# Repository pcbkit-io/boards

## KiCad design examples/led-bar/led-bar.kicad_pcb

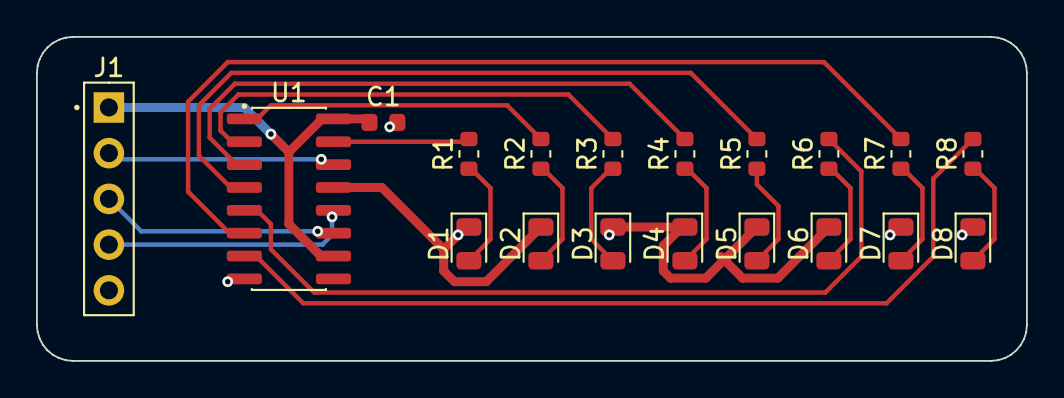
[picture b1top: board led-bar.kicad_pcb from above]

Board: 2 copper layers, 55.0 x 18.0 mm, 19 parts (0 on the bottom side), 21 nets.

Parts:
C1: 100nF; C_0603_1608Metric
D1, D2, D3, D4, D5, D6, D7, D8: green; LED_0805_2012Metric
J1: PinHeader_1x05_P2.54mm_Vertical
R1, R2, R3, R4, R5, R6, R7, R8: 470ohm; R_0603_1608Metric
U1: SN74HC595DR; SOIC-16_3.9x9.9mm_P1.27mm

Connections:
+5V: C1.1 (a), J1.1, U1.10 (SRCLR), U1.16 (VCC)
GND: C1.2 (b), D1.1 (K), D2.1 (K), D3.1 (K), D4.1 (K), D5.1 (K), D6.1 (K), D7.1 (K), D8.1 (K), J1.5, U1.8 (GND), U1.13 (OE)
Q0: R1.2 (b), U1.15 (QA)
Q1: R2.2 (b), U1.1 (QB)
Q2: R3.2 (b), U1.2 (QC)
Q3: R4.2 (b), U1.3 (QD)
Q4: R5.2 (b), U1.4 (QE)
Q5: R6.2 (b), U1.5 (QF)
Q6: R7.2 (b), U1.6 (QG)
Q7: R8.2 (b), U1.7 (QH)
RCLK: J1.4, U1.12 (RCLK)
SER: J1.2, U1.14 (SER)
SRCLK: J1.3, U1.11 (SRCLK)
leds[1]/anode: D1.2 (A), R1.1 (a)
leds[2]/anode: D2.2 (A), R2.1 (a)
leds[3]/anode: D3.2 (A), R3.1 (a)
leds[4]/anode: D4.2 (A), R4.1 (a)
leds[5]/anode: D5.2 (A), R5.1 (a)
leds[6]/anode: D6.2 (A), R6.1 (a)
leds[7]/anode: D7.2 (A), R7.1 (a)
leds[8]/anode: D8.2 (A), R8.1 (a)

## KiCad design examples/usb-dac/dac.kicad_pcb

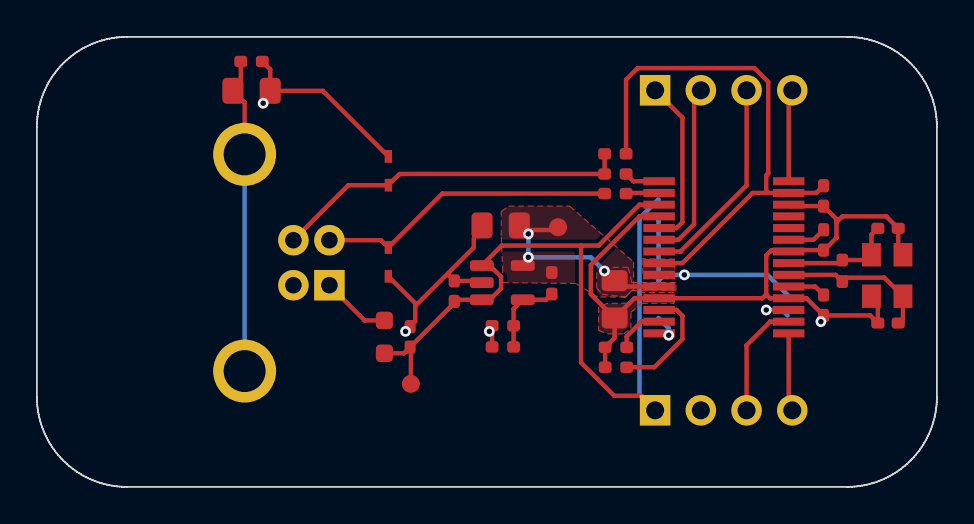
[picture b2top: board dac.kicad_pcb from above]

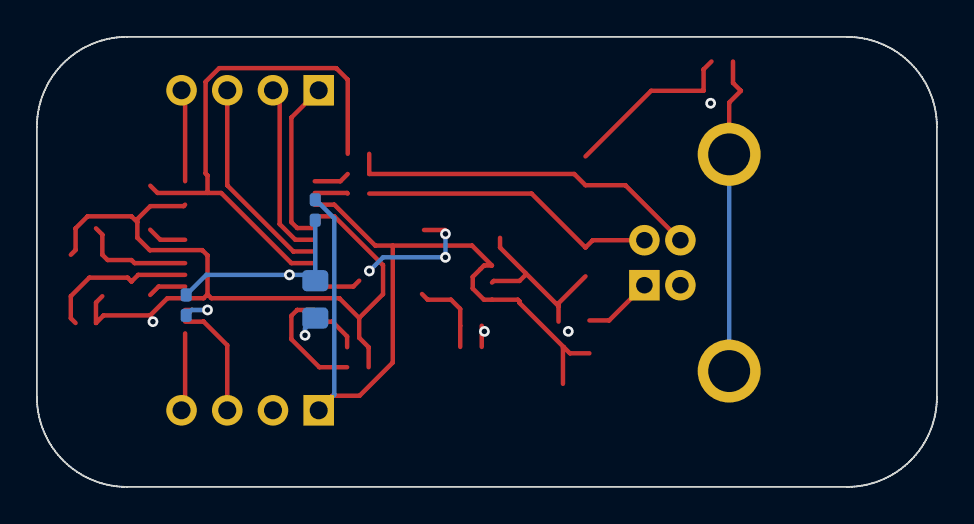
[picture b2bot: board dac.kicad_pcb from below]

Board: 4 copper layers, 50.0 x 25.0 mm, 34 parts (3 on the bottom side), 25 nets.

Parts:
C1, C6, C12: 10u; C_0805_2012Metric_Pad1.18x1.45mm_HandSolder
C2, C3, C4, C5, C7, C11, C13: 1u; C_0402_1005Metric_Pad0.74x0.62mm_HandSolder
C8, C9: 20p; C_0402_1005Metric_Pad0.74x0.62mm_HandSolder
C10: 2n2; C_0805_2012Metric_Pad1.18x1.45mm_HandSolder
D1, D2: ESD321; SOT5x3_DYA_TEX-M
J1: USB_B; USB_B_OST_USB-B1HSxx_Horizontal
J2, J3: Conn_01x04_Pin; PinHeader_1x04_P2.54mm_Vertical
R1, R2: 22R; R_0402_1005Metric_Pad0.72x0.64mm_HandSolder
R3, R4, R6: 1k5; R_0402_1005Metric_Pad0.72x0.64mm_HandSolder
R5: 1M; R_0402_1005Metric_Pad0.72x0.64mm_HandSolder
R7: DNP; R_0402_1005Metric_Pad0.72x0.64mm_HandSolder
R8: 2.2; R_0603_1608Metric_Pad0.98x0.95mm_HandSolder
R9, R10, R11: 10k; R_0402_1005Metric_Pad0.72x0.64mm_HandSolder
TP1, TP2: TestPoint; TestPoint_Pad_D1.0mm
U1: PCM2906C; SSOP-28_5.3x10.2mm_P0.65mm
U2: SPX3819M5-L; SOT-23-5
Y1: 12MHz; XTAL_ABM8-12.000MHZ-12-B1U-T

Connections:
3V7: C6.1, C12.1, R10.1, TP1.1, U1.10, U2.5
/ADJ: R9.1, R10.2, R11.1, U2.4
/CONN_D+: D2.2, J1.3, R1.1, R6.2
/CONN_D-: D1.2, J1.2, R2.1
/HID0: J3.1, U1.5
/HID1: J3.2, U1.6
/HID2: J3.3, U1.7
/USB_D+: R1.2, U1.1
/USB_D-: R2.2, U1.2
/VCCP1I: C2.1, U1.17
/VCCP2I: C3.1, U1.19
/VCCXI: C4.1, U1.23
/VCOM: C1.1, U1.14
/VINL: R4.1, U1.12
/VINR: R3.1, U1.13
/VOUTL: J2.3, U1.16
/VOUTR: J2.4, U1.15
/XTI: C9.1, R5.2, U1.21, Y1.3
/XTO: C8.1, R5.1, U1.20, Y1.1
/~SSPND: J3.4, U1.28
CGND: C10.1, J1.5, R7.1
GND: C1.2, C2.2, C3.2, C4.2, C5.2, C6.2, C7.2, C8.2, C9.2, C10.2, C11.2, C12.2, C13.2, D1.1, D2.1, J1.4, J2.2, R3.2, R4.2, R7.2, R9.2, R11.2, U1.4, U1.11, U1.18, U1.22, U1.26, U2.2, Y1.2, Y1.4
VBUS: C7.1, C11.1, C13.1, J2.1, R8.2, TP2.1, U1.3, U2.1, U2.3
VDDI: C5.1, R6.1, U1.8, U1.9, U1.27
VUSB_CONN: J1.1, R8.1

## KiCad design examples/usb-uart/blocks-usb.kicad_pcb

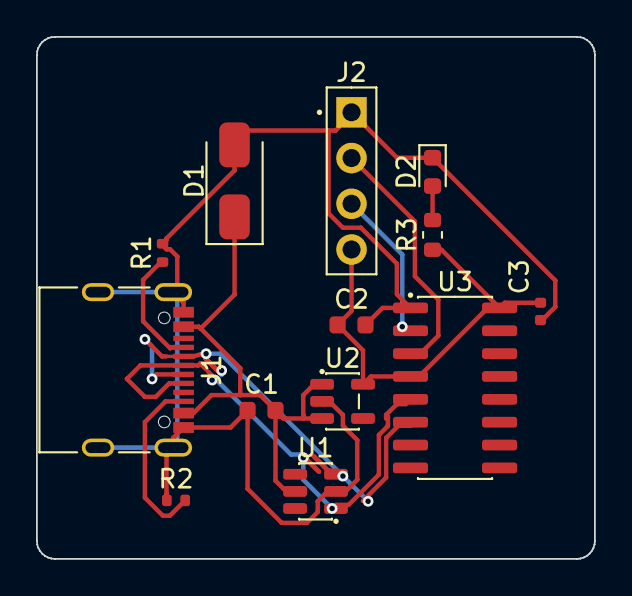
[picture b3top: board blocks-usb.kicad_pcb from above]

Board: 2 copper layers, 31.0 x 29.0 mm, 13 parts (0 on the bottom side), 10 nets.

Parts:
C1, C2: 1uF; C_0603_1608Metric
C3: 100nF; C_0402_1005Metric
D1: tvs 5V; D_SMA
D2: green; LED_0603_1608Metric
J1: USB4105-GF-A; USB_C_Receptacle_USB2.0_16P
J2: PinHeader_1x04_P2.54mm_Vertical
R1, R2: 5.1kohm; R_0402_1005Metric
R3: 300ohm; R_0603_1608Metric
U1: USBLC6-2SC6; SOT-23-6
U2: AP2112K-3.3TRG1; SOT-23-5
U3: CH340C; SOIC-16_3.9x9.9mm_P1.27mm

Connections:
DN: J1.A7 (DN), J1.B7 (DN), U1.3 (IO2), U3.6 (UDN)
DP: J1.A6 (DP), J1.B6 (DP), U1.1 (IO1), U3.5 (UDP)
GND: C1.2 (b), C2.2 (b), C3.2 (b), D1.2 (A), D2.1 (K), J1.A1 (GND), J1.A12, J1.B1 (GND), J1.B12, J1.S1 (SHIELD), J2.1, R1.2 (b), R2.2 (b), U1.2 (GND), U2.2 (GND), U3.1 (GND)
RX: J2.2, U3.3 (RXD)
TX: J2.3, U3.2 (TXD)
V3: C2.1 (a), C3.1 (a), J2.4, R3.1 (a), U2.5 (OUT), U3.4 (V3), U3.16 (VCC)
VBUS: C1.1 (a), D1.1 (K), J1.A4 (VBUS), J1.A9, J1.B4 (VBUS), J1.B9, U1.5 (VBUS), U2.1 (IN), U2.3 (EN)
power/node: D2.2 (A), R3.2 (b)
usb/power/cc1: J1.A5 (CC1), R1.1 (a)
usb/power/cc2: J1.B5 (CC2), R2.1 (a)

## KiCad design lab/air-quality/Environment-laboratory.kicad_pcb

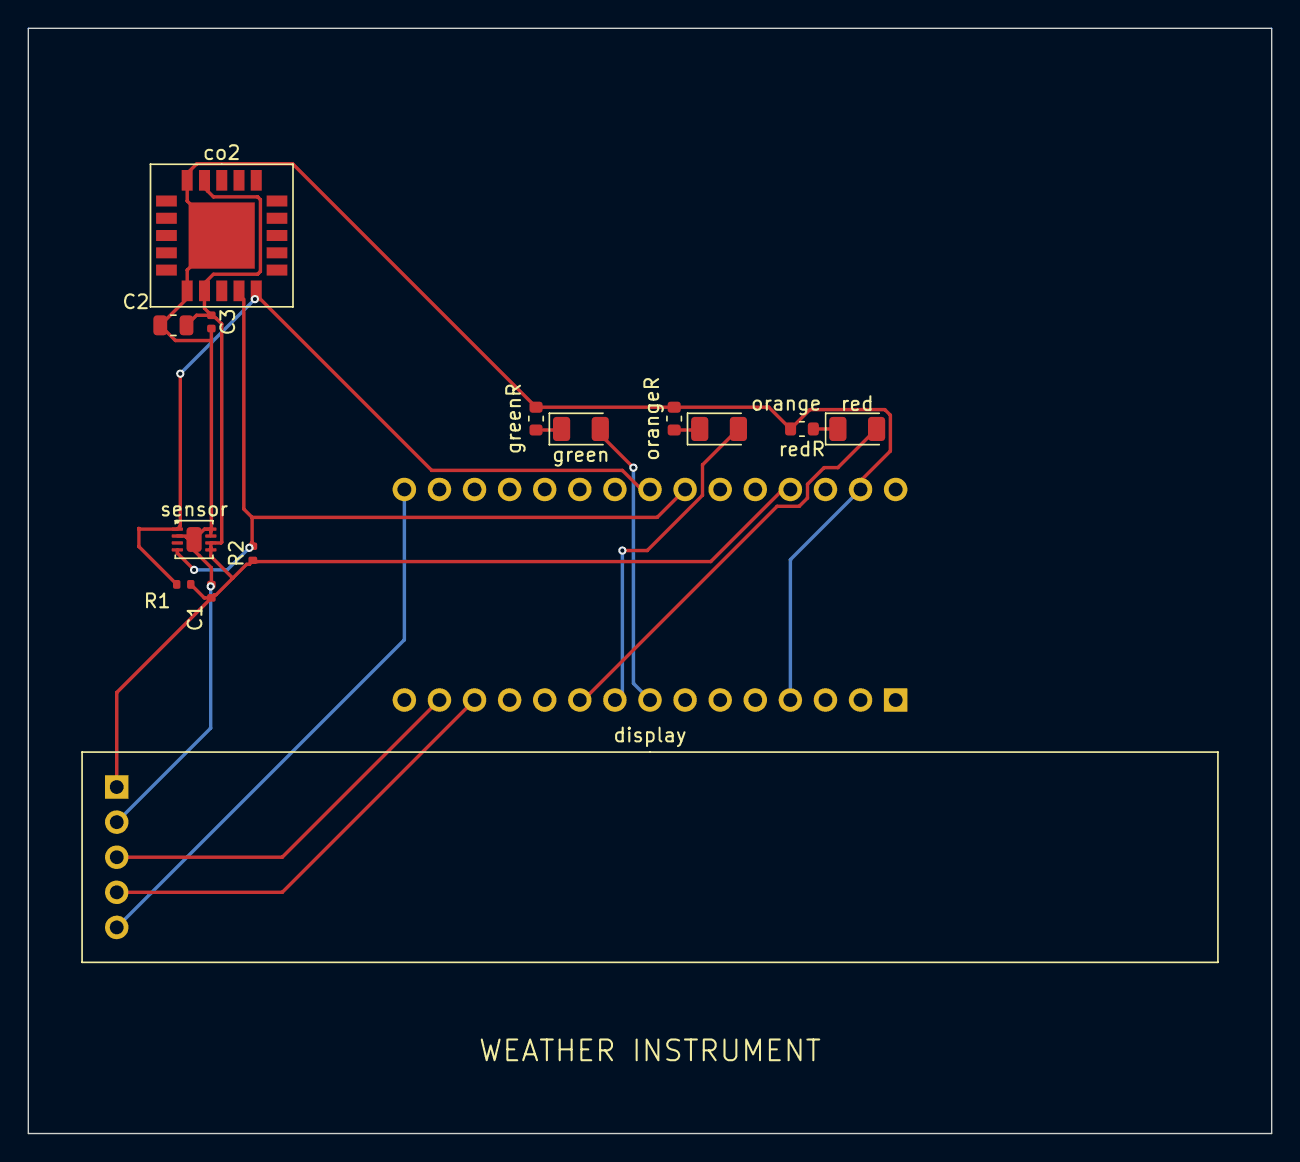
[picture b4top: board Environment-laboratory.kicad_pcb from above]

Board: 2 copper layers, 90.0 x 80.0 mm, 15 parts (1 on the bottom side), 13 nets.

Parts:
C1, C3: 100nF; C_0402_1005Metric
C2: 10uF; C_0805_2012Metric
R1, R2: 10kohm; R_0402_1005Metric
U1: A000005; Arduino_Nano_Socket_2x15_P2.54mm_W15.24mm
co2: SCD40-D-R2; LGA-21_10.1x10.1mm_SCD4x_20_pads_and_a_centre_pad
display: MAX7219 8-digit 7-segment LED display module; MAX7219_8digit_Module_Socket_1x05_P2.54mm
green: green; LED_1206_3216Metric
greenR: 1kohm; R_0603_1608Metric
orange: orange; LED_1206_3216Metric
orangeR: 1kohm; R_0603_1608Metric
red: red; LED_1206_3216Metric
redR: 1kohm; R_0603_1608Metric
sensor: SHT31-DIS-B2.5kS; DFN-8-1EP_2.5x2.5mm_P0.5mm_EP1.1x1.8mm

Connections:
GND: C1.1 (a), C2.2 (b), C3.2 (b), U1.4 (GND), U1.29 (GND), co2.6 (GND), co2.20 (GND), co2.21 (GND), display.2 (GND), greenR.2 (b), orangeR.2 (b), redR.2 (b), sensor.2 (ADDR), sensor.7 (R), sensor.8 (VSS), sensor.9 (VSS)
GREEN: U1.8 (D5), green.2 (A)
GREEN_K: green.1 (K), greenR.1 (a)
LOAD: U1.13 (D10), display.4 (CS)
MOSI: U1.14 (D11), display.3 (DIN)
ORANGE: U1.9 (D6), orange.2 (A)
ORANGE_K: orange.1 (K), orangeR.1 (a)
RED: U1.10 (D7), red.2 (A)
RED_K: red.1 (K), redR.1 (a)
SCK: U1.16 (D13), display.5 (CLK)
SCL: R2.1 (a), U1.24 (A5), co2.9 (SCL), sensor.4 (SCL)
SDA: R1.2 (b), U1.23 (A4), co2.10 (SDA), sensor.1 (SDA)
V5: C1.2 (b), C2.1 (a), C3.1 (a), R1.1 (a), R2.2 (b), U1.27 (P5V), co2.7 (VDD), co2.19 (VDDH), display.1 (VCC), sensor.5 (VDD), sensor.6 (nRESET)

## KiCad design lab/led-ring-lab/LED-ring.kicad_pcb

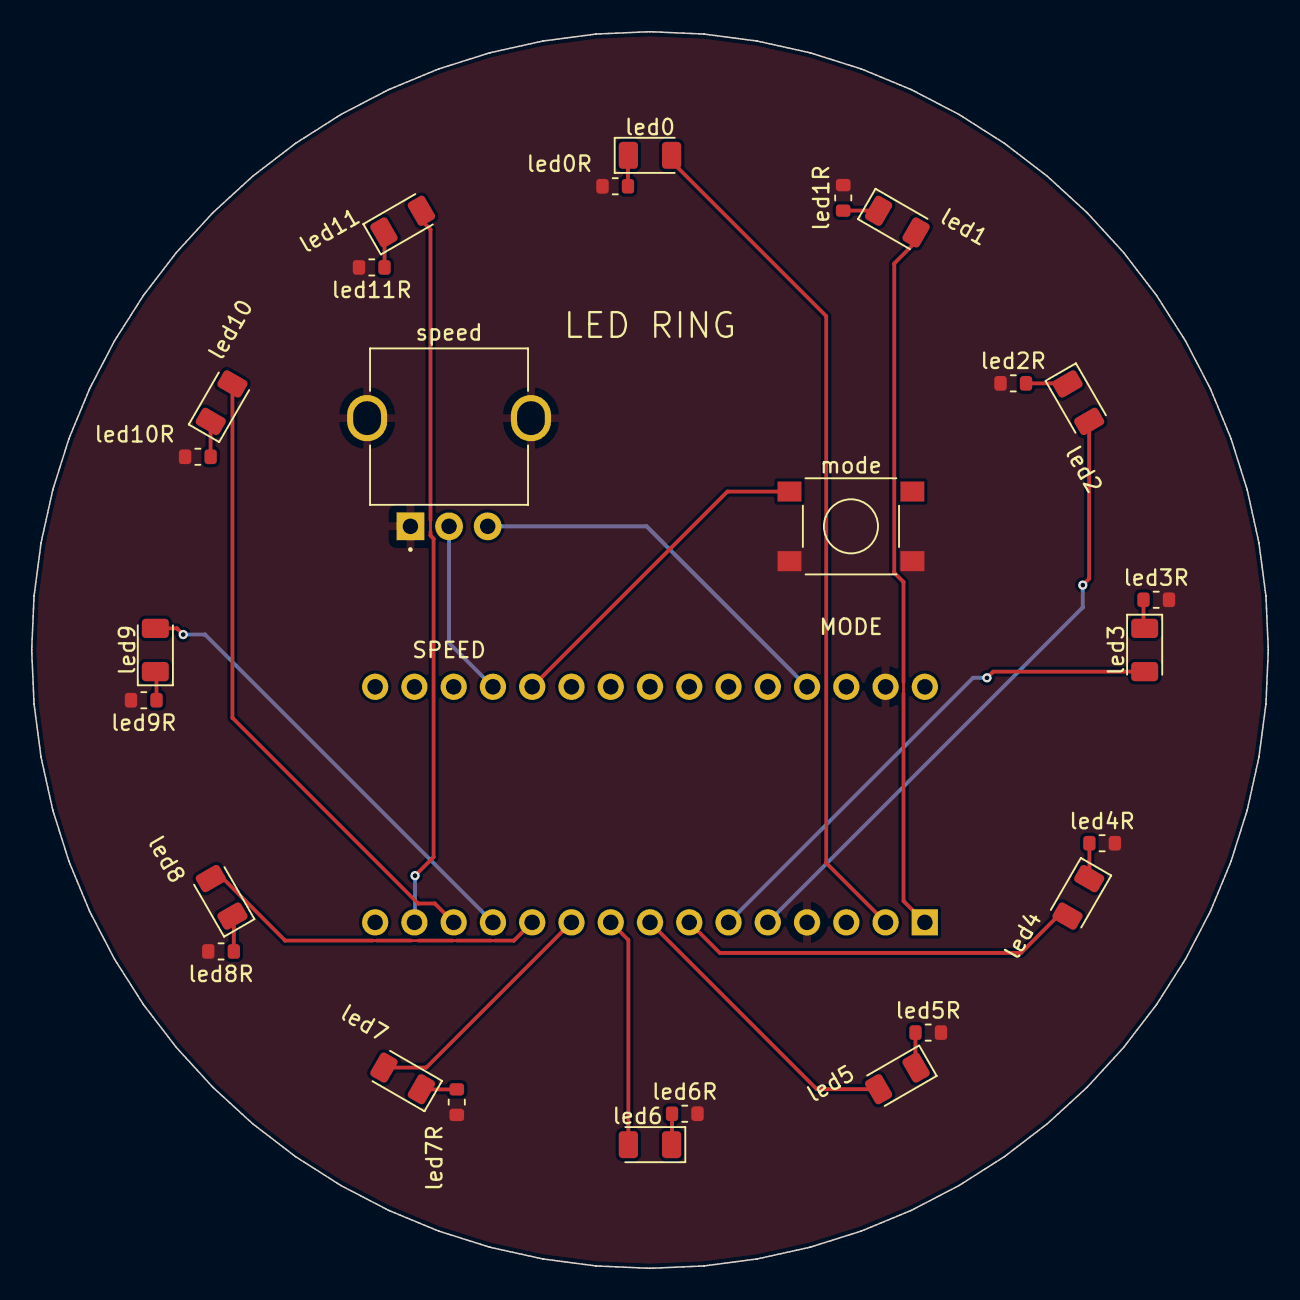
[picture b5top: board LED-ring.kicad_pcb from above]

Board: 2 copper layers, 80.0 x 80.0 mm, 27 parts (1 on the bottom side), 28 nets.

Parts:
U1: A000005; Arduino_Nano_Socket_2x15_P2.54mm_W15.24mm
led0, led1, led2, led3: green; LED_1206_3216Metric
led0R, led1R, led2R, led3R, led4R, led5R, led6R, led7R, led8R, led9R, led10R, led11R: 1kohm; R_0603_1608Metric
led4, led5, led6, led7: orange; LED_1206_3216Metric
led8, led9, led10, led11: red; LED_1206_3216Metric
mode: PTS645SM43SMTR92 LFS; SW_Tactile_SPST_6x6mm_SMD
speed: PTV09A-4020F-B103; Potentiometer_Bourns_PTV09A-4_Vertical

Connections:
GND: U1.4 (GND), U1.29 (GND), led0R.2 (b), led1R.2 (b), led2R.2 (b), led3R.2 (b), led4R.2 (b), led5R.2 (b), led6R.2 (b), led7R.2 (b), led8R.2 (b), led9R.2 (b), led10R.2 (b), led11R.2 (b), mode.2 (b), speed.1 (CCW), speed.MP
L0: U1.2 (D0), led0.2 (A)
L0_K: led0.1 (K), led0R.1 (a)
L1: U1.1 (D1), led1.2 (A)
L1_K: led1.1 (K), led1R.1 (a)
L2: U1.5 (D2), led2.2 (A)
L2_K: led2.1 (K), led2R.1 (a)
L3: U1.6 (D3), led3.2 (A)
L3_K: led3.1 (K), led3R.1 (a)
L4: U1.7 (D4), led4.2 (A)
L4_K: led4.1 (K), led4R.1 (a)
L5: U1.8 (D5), led5.2 (A)
L5_K: led5.1 (K), led5R.1 (a)
L6: U1.9 (D6), led6.2 (A)
L6_K: led6.1 (K), led6R.1 (a)
L7: U1.10 (D7), led7.2 (A)
L7_K: led7.1 (K), led7R.1 (a)
L8: U1.11 (D8), led8.2 (A)
L8_K: led8.1 (K), led8R.1 (a)
L9: U1.12 (D9), led9.2 (A)
L9_K: led9.1 (K), led9R.1 (a)
L10: U1.13 (D10), led10.2 (A)
L10_K: led10.1 (K), led10R.1 (a)
L11: U1.14 (D11), led11.2 (A)
L11_K: led11.1 (K), led11R.1 (a)
MODE: U1.20 (A1), mode.1 (a)
SPEED: U1.19 (A0), speed.2 (W)
V5: U1.27 (P5V), speed.3 (CW)

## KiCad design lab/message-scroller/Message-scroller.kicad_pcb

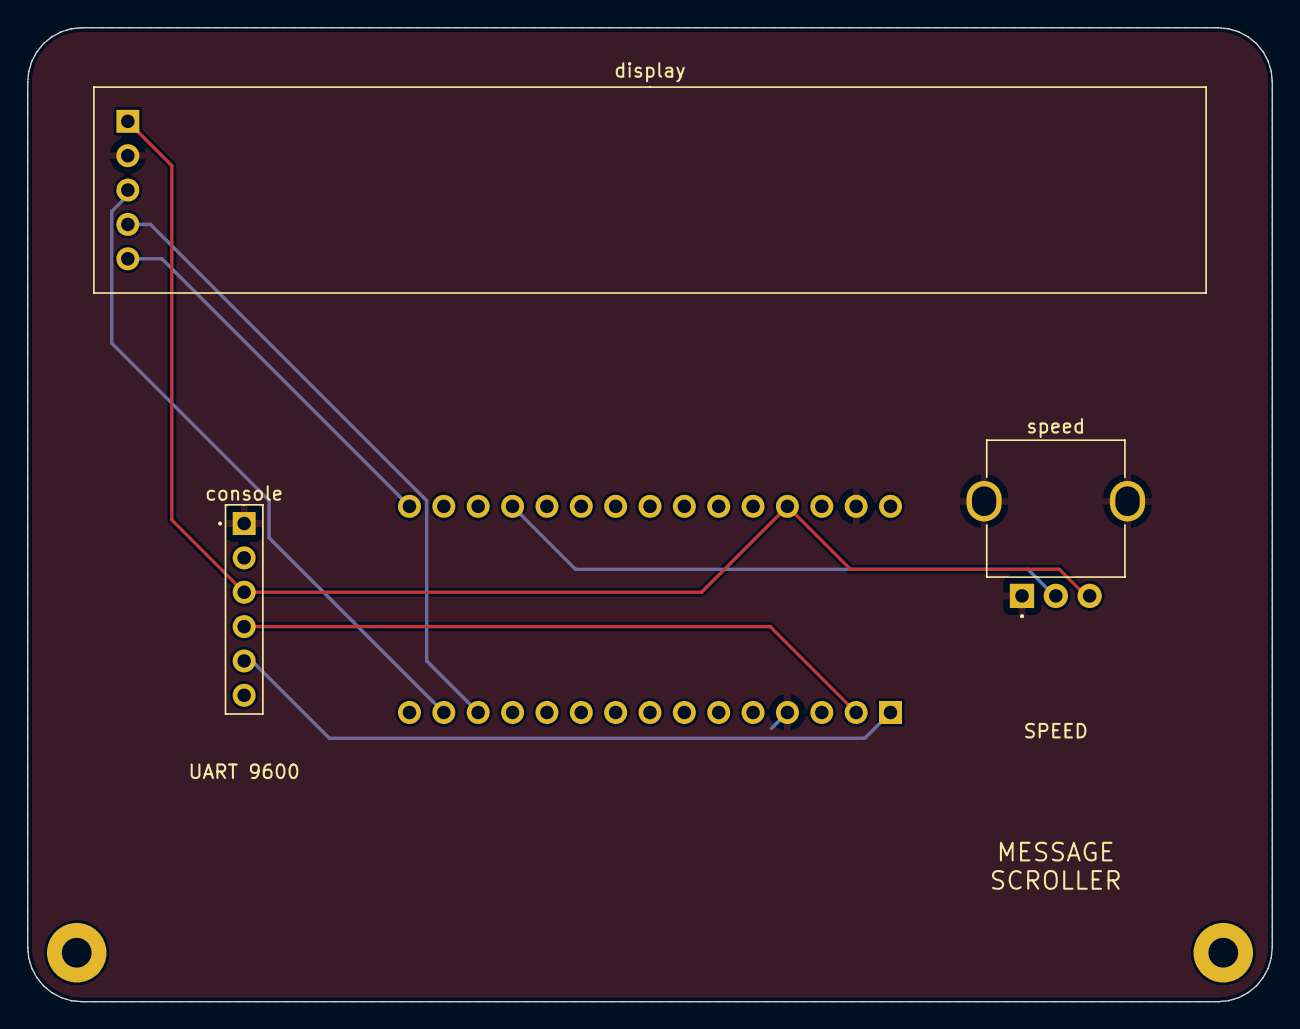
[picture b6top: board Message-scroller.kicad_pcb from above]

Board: 2 copper layers, 92.0 x 72.0 mm, 6 parts (1 on the bottom side), 8 nets.

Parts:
H1, H2: MountingHole_2.2mm_M2_Pad
U1: A000005; Arduino_Nano_Socket_2x15_P2.54mm_W15.24mm
console: PinHeader_1x06_P2.54mm_Vertical
display: MAX7219 8-digit 7-segment LED display module; MAX7219_8digit_Module_Socket_1x05_P2.54mm
speed: PTV09A-4020F-B103; Potentiometer_Bourns_PTV09A-4_Vertical

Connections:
GND: U1.4 (GND), U1.29 (GND), console.1, display.2 (GND), speed.1 (CCW), speed.MP
LOAD: U1.13 (D10), display.4 (CS)
MOSI: U1.14 (D11), display.3 (DIN)
RX: U1.2 (D0), console.4
SCK: U1.16 (D13), display.5 (CLK)
SPEED: U1.19 (A0), speed.2 (W)
TX: U1.1 (D1), console.5
V5: U1.27 (P5V), console.3, display.1 (VCC), speed.3 (CW)

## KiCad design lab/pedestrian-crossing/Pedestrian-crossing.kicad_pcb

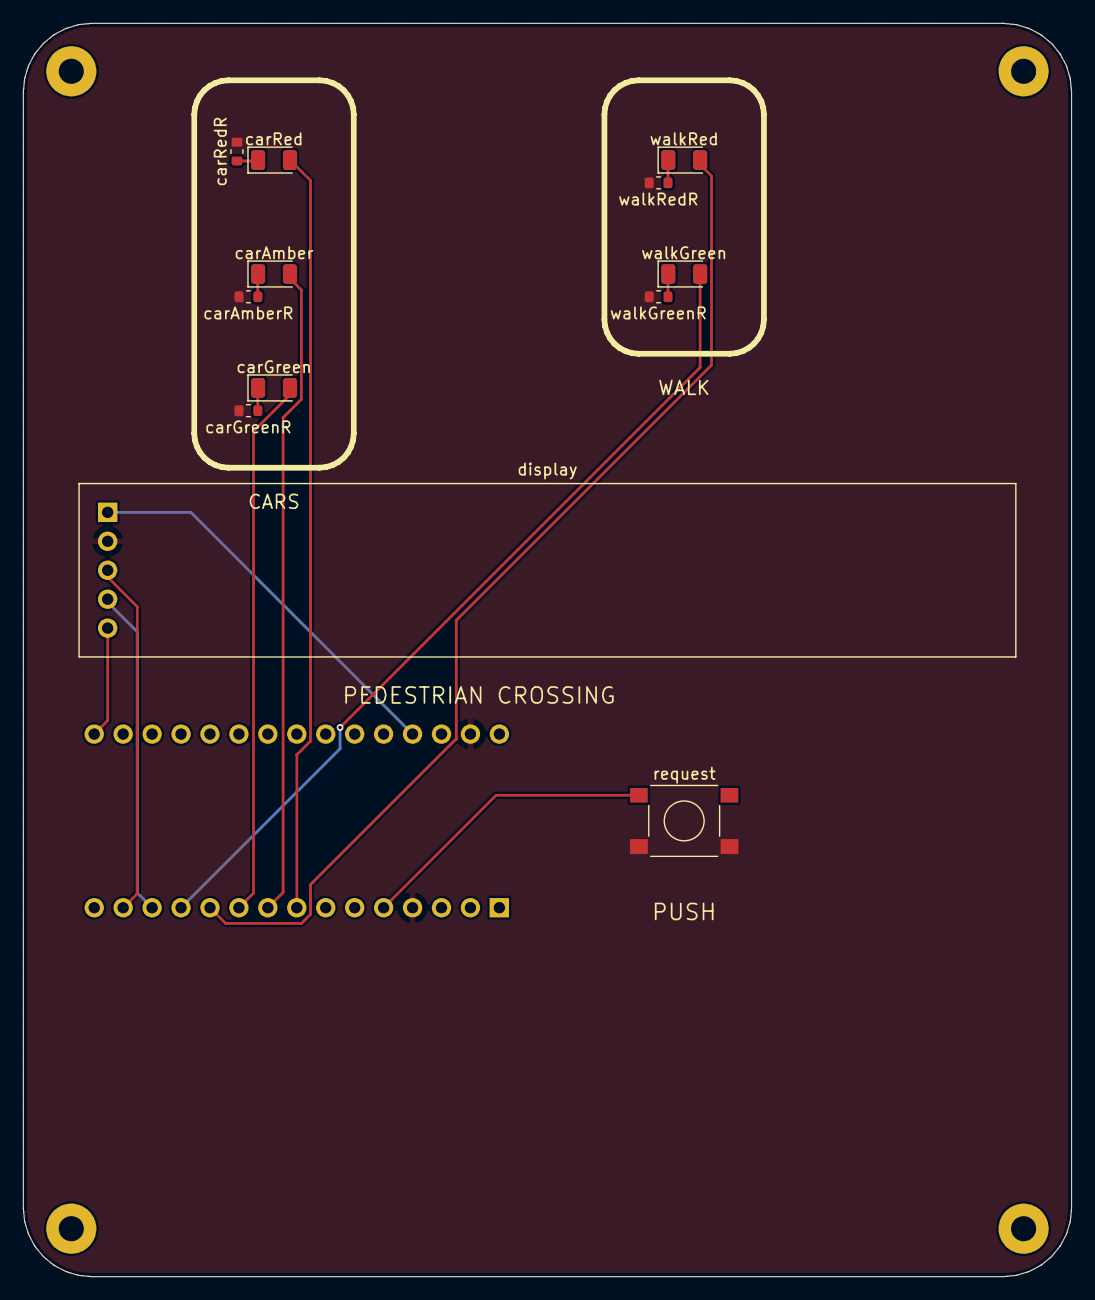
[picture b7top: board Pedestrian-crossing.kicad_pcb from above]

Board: 2 copper layers, 92.0 x 110.0 mm, 17 parts (1 on the bottom side), 16 nets.

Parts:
H1, H2, H3, H4: MountingHole_2.2mm_M2_Pad
U1: A000005; Arduino_Nano_Socket_2x15_P2.54mm_W15.24mm
carAmber: orange; LED_1206_3216Metric
carAmberR: 1kohm; R_0603_1608Metric
carGreen: green; LED_1206_3216Metric
carGreenR: 1kohm; R_0603_1608Metric
carRed: red; LED_1206_3216Metric
carRedR: 1kohm; R_0603_1608Metric
display: MAX7219 8-digit 7-segment LED display module; MAX7219_8digit_Module_Socket_1x05_P2.54mm
request: PTS645SM43SMTR92 LFS; SW_Tactile_SPST_6x6mm_SMD
walkGreen: green; LED_1206_3216Metric
walkGreenR: 1kohm; R_0603_1608Metric
walkRed: red; LED_1206_3216Metric
walkRedR: 1kohm; R_0603_1608Metric

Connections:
CAR_AMBER: U1.9 (D6), carAmber.2 (A)
CAR_AMBER_K: carAmber.1 (K), carAmberR.1 (a)
CAR_GREEN: U1.10 (D7), carGreen.2 (A)
CAR_GREEN_K: carGreen.1 (K), carGreenR.1 (a)
CAR_RED: U1.8 (D5), carRed.2 (A)
CAR_RED_K: carRed.1 (K), carRedR.1 (a)
GND: U1.4 (GND), U1.29 (GND), carAmberR.2 (b), carGreenR.2 (b), carRedR.2 (b), display.2 (GND), request.2 (b), walkGreenR.2 (b), walkRedR.2 (b)
LOAD: U1.13 (D10), display.4 (CS)
MOSI: U1.14 (D11), display.3 (DIN)
REQUEST: U1.5 (D2), request.1 (a)
SCK: U1.16 (D13), display.5 (CLK)
V5: U1.27 (P5V), display.1 (VCC)
WALK_GREEN: U1.12 (D9), walkGreen.2 (A)
WALK_GREEN_K: walkGreen.1 (K), walkGreenR.1 (a)
WALK_RED: U1.11 (D8), walkRed.2 (A)
WALK_RED_K: walkRed.1 (K), walkRedR.1 (a)
